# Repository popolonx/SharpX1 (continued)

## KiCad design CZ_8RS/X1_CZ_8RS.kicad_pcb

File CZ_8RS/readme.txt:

Kicad files (kicad version 5.1.5) for CZ-8RS RS-232 board.
Based on the http://www.x1center.org/resource/schematic/CZ8RS_Schematic.pdf
-at least one error corrected (IC6-pin4:  RESET -> IOEX )

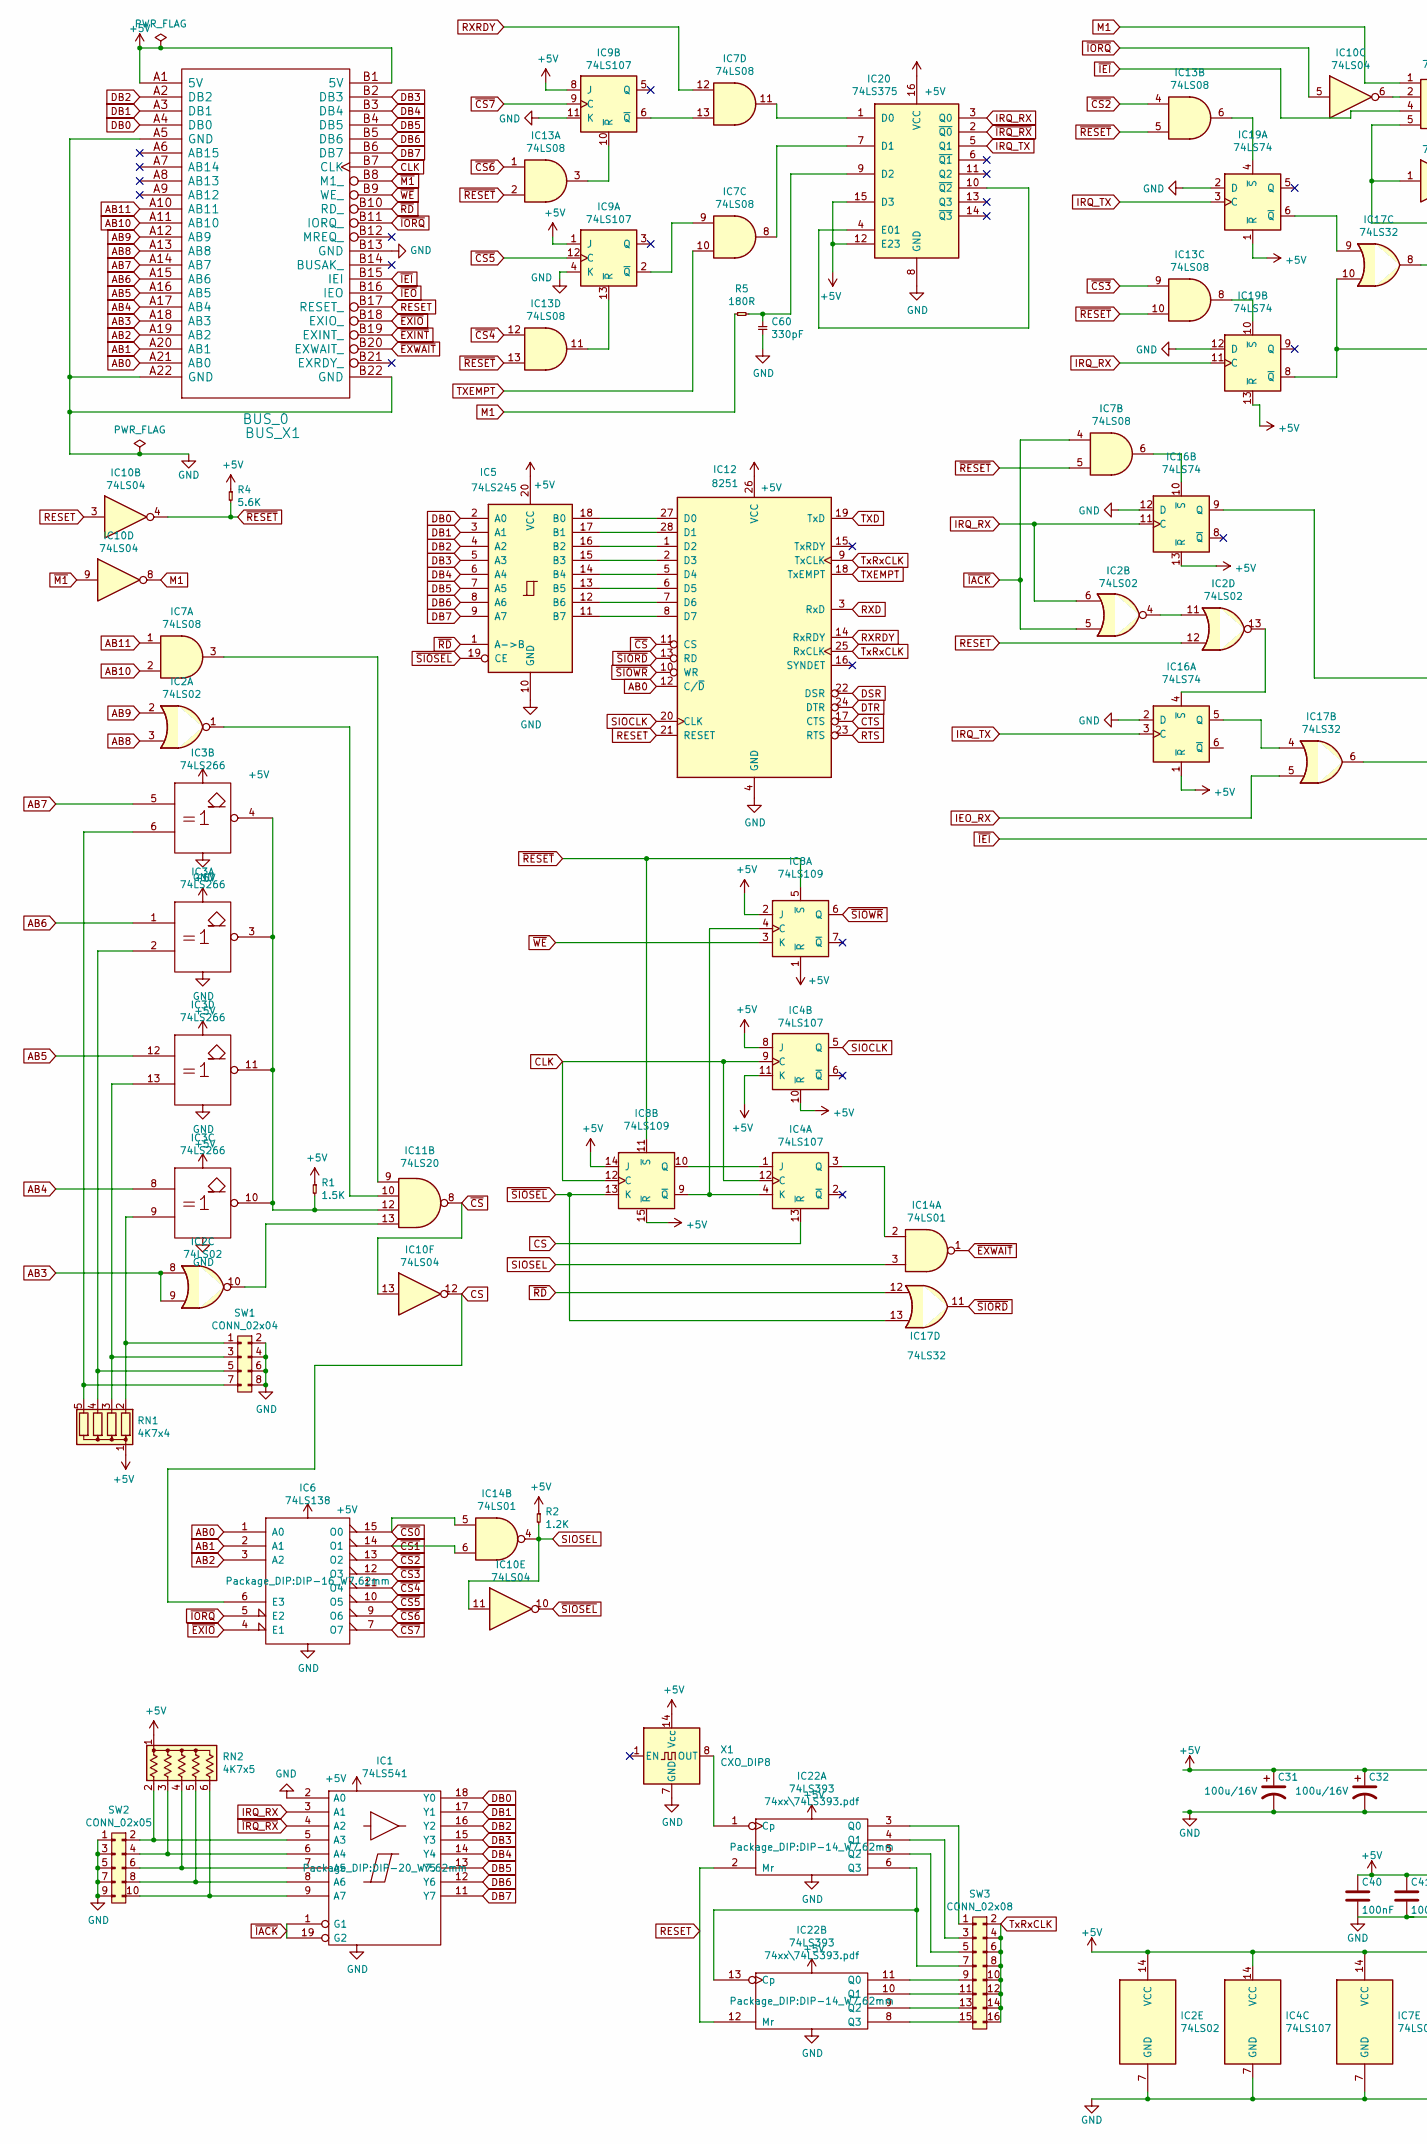
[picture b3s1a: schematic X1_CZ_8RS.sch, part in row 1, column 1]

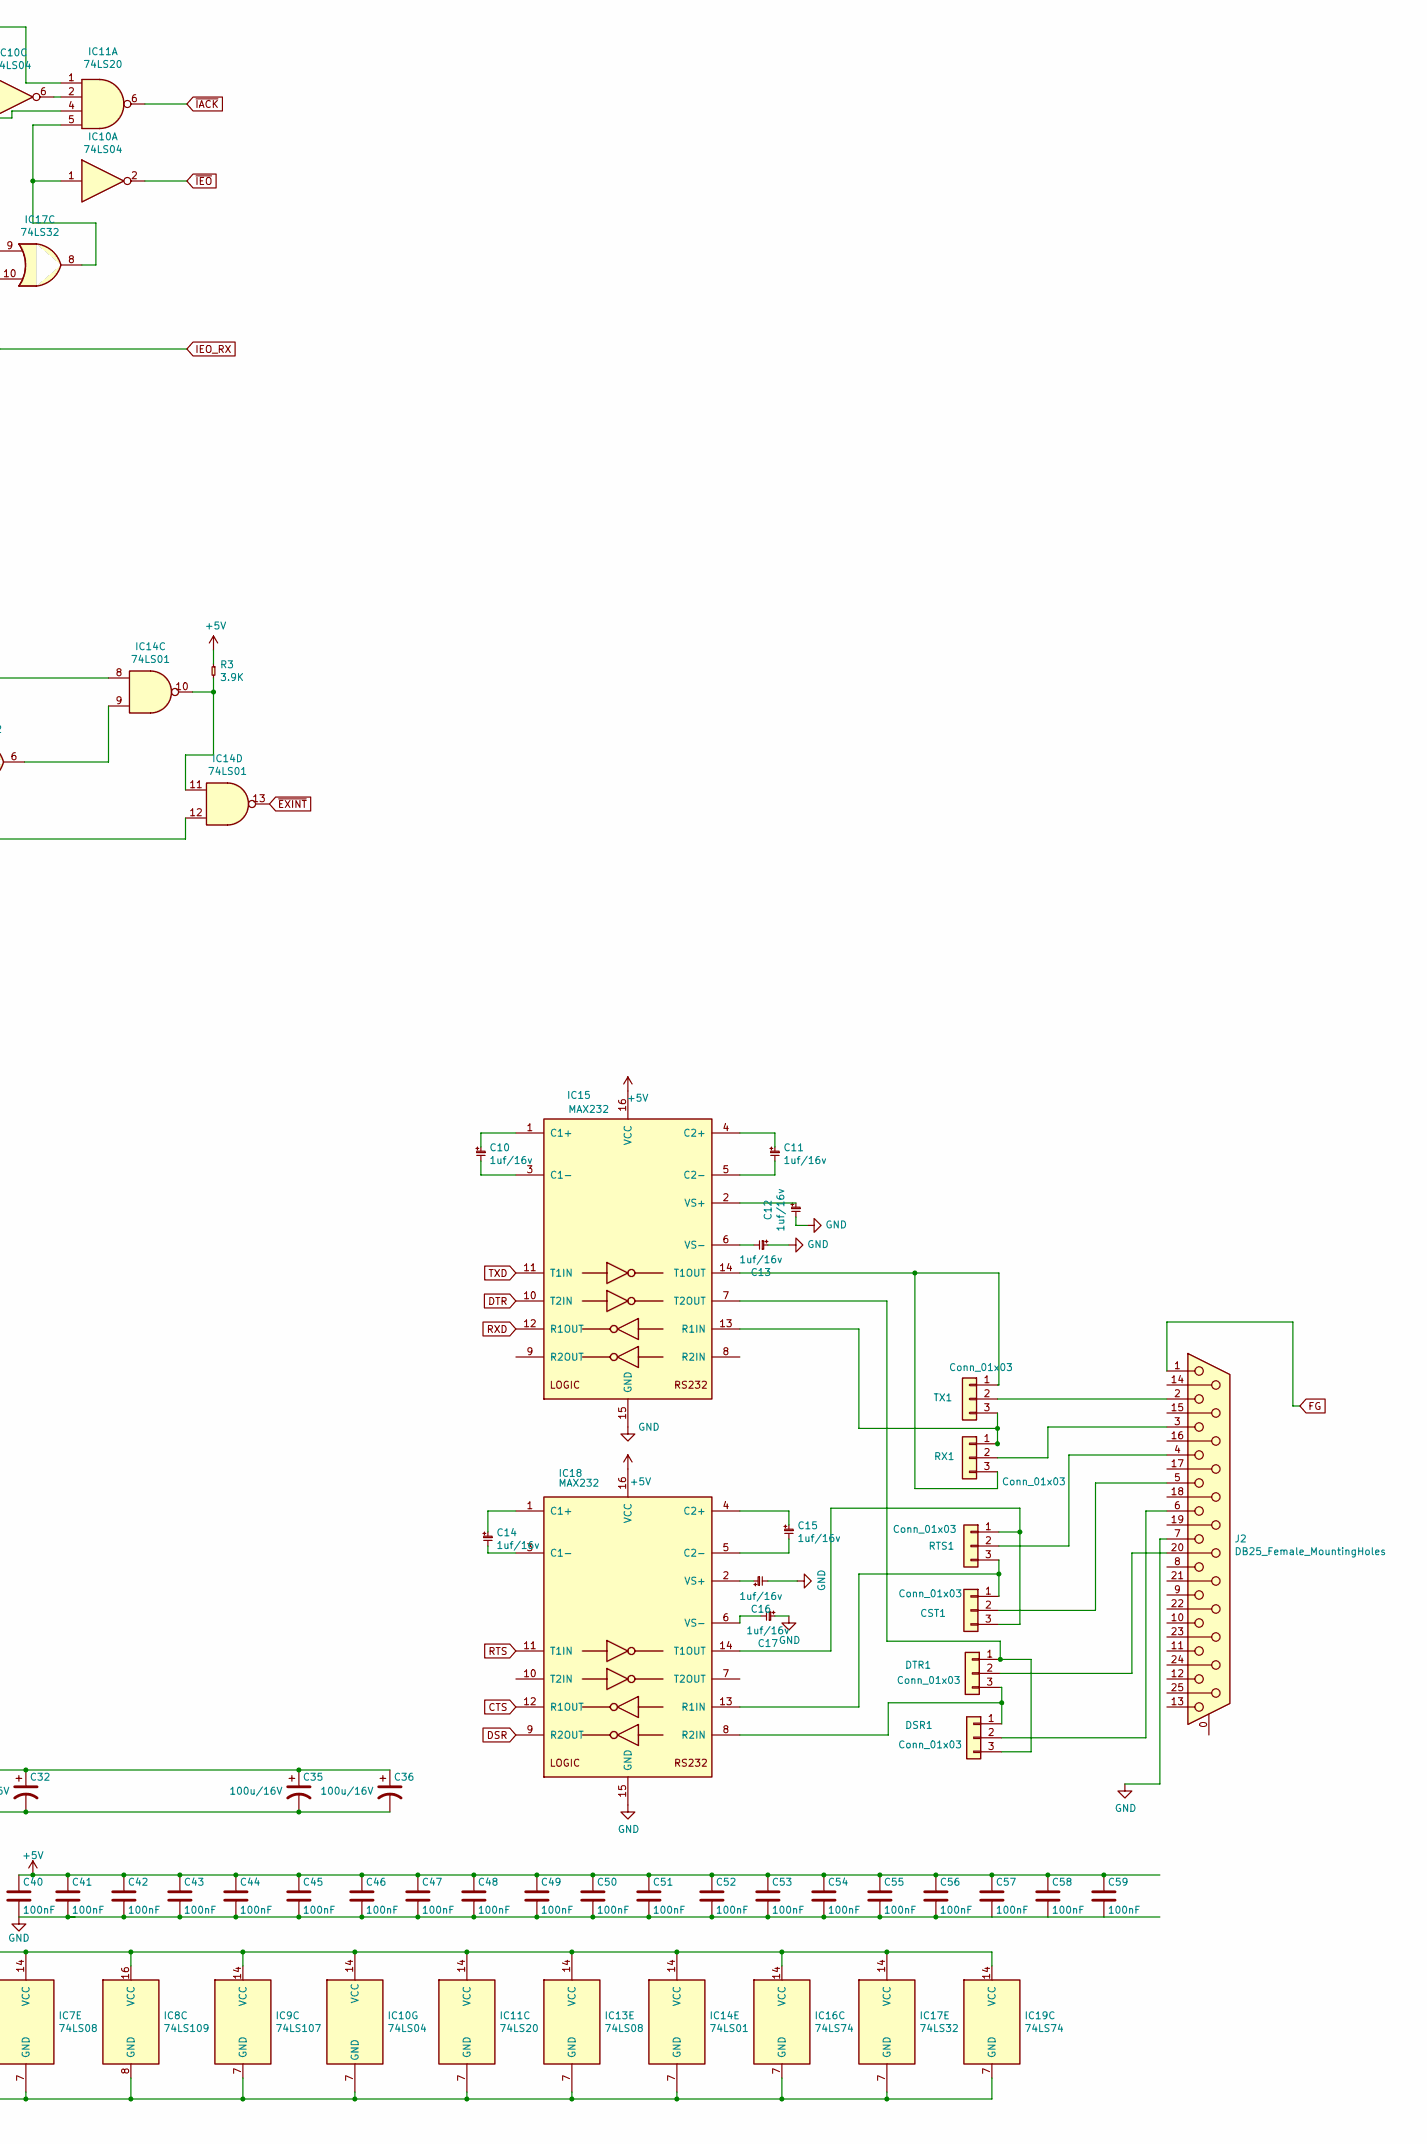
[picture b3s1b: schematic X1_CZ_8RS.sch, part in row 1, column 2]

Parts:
BUS_0: BUS_X1; X1_IO
C10, C11, C12, C13, C14, C15, C16, C17: 1uf/16v; CP_Radial_D8.0mm_P2.50mm
C31, C32, C35: 100u/16V; CP_Radial_D8.0mm_P5.00mm
C36: 100u/16V; CP_Radial_D7.5mm_P2.50mm
C40, C41, C42, C43, C44, C45, C46, C47, C48, C49, C50, C51, C52, C53, C54, C55, C56, C57, C58, C59: 100nF; C_Disc_D5.0mm_W2.5mm_P5.00mm
C60: 330pF; C_Disc_D5.0mm_W2.5mm_P5.00mm
CST1: Conn_01x03; PinHeader_1x03_P2.54mm_Vertical
DSR1: Conn_01x03; PinHeader_1x03_P2.54mm_Vertical
DTR1: Conn_01x03; PinHeader_1x03_P2.54mm_Vertical
IC1: 74LS541; DIP-20_W7.62mm
IC2: 74LS02; DIP-14_W7.62mm
IC3: 74LS266; DIP-14_W7.62mm
IC4, IC9: 74LS107; DIP-14_W7.62mm
IC5: 74LS245; DIP-20_W7.62mm
IC6: 74LS138; DIP-16_W7.62mm
IC7, IC13: 74LS08; DIP-14_W7.62mm
IC8: 74LS109; DIP-16_W7.62mm
IC10: 74LS04; DIP-14_W7.62mm
IC11: 74LS20; DIP-14_W7.62mm
IC12: 8251; DIP-28_W15.24mm
IC14: 74LS01; DIP-14_W7.62mm
IC15, IC18: MAX232; DIP-16_W7.62mm
IC16, IC19: 74LS74; DIP-14_W7.62mm
IC17: 74LS32; DIP-14_W7.62mm
IC20: 74LS375; DIP-16_W7.62mm
IC22: 74LS393; DIP-14_W7.62mm
J2: DB25_Female_MountingHoles; DSUB-25_Female_Horizontal_P2.77x2.84mm_EdgePinOffset4.94mm_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
R1: 1.5K; R_Axial_DIN0309_L9.0mm_D3.2mm_P12.70mm_Horizontal
R2: 1.2K; R_Axial_DIN0309_L9.0mm_D3.2mm_P12.70mm_Horizontal
R3: 3.9K; R_Axial_DIN0309_L9.0mm_D3.2mm_P12.70mm_Horizontal
R4: 5.6K; R_Axial_DIN0309_L9.0mm_D3.2mm_P12.70mm_Horizontal
R5: 180R; R_Axial_DIN0309_L9.0mm_D3.2mm_P12.70mm_Horizontal
RN1: 4K7x4; R_Array_SIP5
RN2: 4K7x5; R_Array_SIP6
RTS1: Conn_01x03; PinHeader_1x03_P2.54mm_Vertical
RX1: Conn_01x03; PinHeader_1x03_P2.54mm_Vertical
SW1: CONN_02x04; PinHeader_2x04_P2.54mm_Vertical
SW2: CONN_02x05; PinHeader_2x05_P2.54mm_Vertical
SW3: CONN_02x08; PinHeader_2x08_P2.54mm_Vertical
TX1: Conn_01x03; PinHeader_1x03_P2.54mm_Vertical
X1: CXO_DIP8; Oscillator_DIP-14

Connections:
+5V: BUS_0.A1 (5V), BUS_0.B1 (5V), C31.1, C32.1, C35.1, C36.1, C40.1, C41.1, C42.1, C43.1, C44.1, C45.1, C46.1, C47.1, C48.1, C49.1, C50.1, C51.1, C52.1, C53.1, C54.1, C55.1, C56.1, C57.1, C58.1, C59.1, IC1.20 (VCC), IC2.14 (VCC), IC3.14 (VCC), IC4.8 (J), IC4.10 (~R), IC4.11 (K), IC4.14 (VCC), IC5.20 (VCC), IC6.16 (VCC), IC7.14 (VCC), IC8.1 (~R), IC8.2 (J), IC8.14 (J), IC8.15 (~R), IC8.16 (VCC), IC9.1 (J), IC9.8 (J), IC9.14 (VCC), IC10.14 (VCC), IC11.14 (VCC), IC12.26 (VCC), IC13.14 (VCC), IC14.14 (VCC), IC15.16 (VCC), IC16.1 (~R), IC16.13 (~R), IC16.14 (VCC), IC17.14 (VCC), IC18.16 (VCC), IC19.1 (~R), IC19.13 (~R), IC19.14 (VCC), IC20.12 (E23), IC20.15 (D3), IC20.16 (VCC), IC22.14 (VCC), R1.1, R2.1, R3.1, R4.1, RN1.1 (common), RN2.1 (common), X1.14 (Vcc)
AB0: BUS_0.A21 (AB0), IC6.1 (A0), IC12.12 (C/~D)
AB1: BUS_0.A20 (AB1), IC6.2 (A1)
AB2: BUS_0.A19 (AB2), IC6.3 (A2)
AB3: BUS_0.A18 (AB3), IC2.8, IC2.9
AB4: BUS_0.A17 (AB4), IC3.8
AB5: BUS_0.A16 (AB5), IC3.12
AB6: BUS_0.A15 (AB6), IC3.1
AB7: BUS_0.A14 (AB7), IC3.5
AB8: BUS_0.A13 (AB8), IC2.3
AB9: BUS_0.A12 (AB9), IC2.2
AB10: BUS_0.A11 (AB10), IC7.2
AB11: BUS_0.A10 (AB11), IC7.1
CLK: BUS_0.B7 (CLK), IC4.9 (C), IC4.12 (C), IC8.12 (C)
CS: IC4.13 (~R), IC6.6 (E3), IC10.12
CTS: IC12.17 (CTS), IC18.12 (R1OUT)
DB0: BUS_0.A4 (DB0), IC1.18 (Y0), IC5.2 (A0)
DB1: BUS_0.A3 (DB1), IC1.17 (Y1), IC5.3 (A1)
DB2: BUS_0.A2 (DB2), IC1.16 (Y2), IC5.4 (A2)
DB3: BUS_0.B2 (DB3), IC1.15 (Y3), IC5.5 (A3)
DB4: BUS_0.B3 (DB4), IC1.14 (Y4), IC5.6 (A4)
DB5: BUS_0.B4 (DB5), IC1.13 (Y5), IC5.7 (A5)
DB6: BUS_0.B5 (DB6), IC1.12 (Y6), IC5.8 (A6)
DB7: BUS_0.B6 (DB7), IC1.11 (Y7), IC5.9 (A7)
DSR: IC12.22 (DSR), IC18.9 (R2OUT)
DTR: IC12.24 (DTR), IC15.10 (T2IN)
GND: BUS_0.A5 (GND), BUS_0.A22 (GND), BUS_0.B13 (GND), BUS_0.B22 (GND), C12.1, C13.2, C16.1, C17.2, C31.2, C32.2, C35.2, C36.2, C40.2, C41.2, C42.2, C43.2, C44.2, C45.2, C46.2, C47.2, C48.2, C49.2, C50.2, C51.2, C52.2, C53.2, C54.2, C55.2, C56.2, C57.2, C58.2, C59.2, C60.2, IC1.2 (A0), IC1.10 (GND), IC2.7 (GND), IC3.7 (GND), IC4.7 (GND), IC5.10 (GND), IC6.8 (GND), IC7.7 (GND), IC8.8 (GND), IC9.4 (K), IC9.7 (GND), IC9.11 (K), IC10.7 (GND), IC11.7 (GND), IC12.4 (GND), IC13.7 (GND), IC14.7 (GND), IC15.15 (GND), IC16.2 (D), IC16.7 (GND), IC16.12 (D), IC17.7 (GND), IC18.15 (GND), IC19.2 (D), IC19.7 (GND), IC19.12 (D), IC20.8 (GND), IC22.7 (GND), J2.7, SW1.2, SW1.4, SW1.6, SW1.8, SW2.1, SW2.3, SW2.5, SW2.7, SW2.9, X1.7 (GND)
IEO_RX: IC17.5, IC17.10, IC19.8 (~Q)
IRQ_RX: IC1.3 (A1), IC2.6, IC16.11 (C), IC19.11 (C), IC20.3 (Q0)
IRQ_TX: IC16.3 (C), IC19.3 (C), IC20.5 (Q1)
M1: IC10.8, IC11.1, R5.1
unnamed: C10.1, IC15.3 (C1-)
unnamed: C10.2, IC15.1 (C1+)
unnamed: C11.1, IC15.5 (C2-)
unnamed: C11.2, IC15.4 (C2+)
unnamed: C12.2, IC15.2 (VS+)
unnamed: C13.1, IC15.6 (VS-)
unnamed: C14.1, IC18.3 (C1-)
unnamed: C14.2, IC18.1 (C1+)
unnamed: C15.1, IC18.5 (C2-)
unnamed: C15.2, IC18.4 (C2+)
unnamed: C16.2, IC18.2 (VS+)
unnamed: C17.1, IC18.6 (VS-)
unnamed: C60.1, IC20.9 (D2), R5.2
unnamed: CST1.1, IC18.13 (R1IN), RTS1.3
unnamed: CST1.2, J2.5
unnamed: CST1.3, IC18.14 (T1OUT), RTS1.1
unnamed: DSR1.1, DTR1.3, IC18.8 (R2IN)
unnamed: DSR1.2, J2.6
unnamed: DSR1.3, DTR1.1, IC15.7 (T2OUT)
unnamed: DTR1.2, J2.20
unnamed: IC1.5 (A3), RN2.2 (R1), SW2.2
unnamed: IC1.6 (A4), RN2.3 (R2), SW2.4
unnamed: IC1.7 (A5), RN2.4 (R3), SW2.6
unnamed: IC1.8 (A6), RN2.5 (R4), SW2.8
unnamed: IC1.9 (A7), RN2.6 (R5), SW2.10
unnamed: IC2.4, IC2.11
unnamed: IC3.2, RN1.4 (R3), SW1.5
unnamed: IC3.6, RN1.5 (R4), SW1.7
unnamed: IC3.9, RN1.2 (R1), SW1.1
unnamed: IC3.13, RN1.3 (R2), SW1.3
unnamed: IC4.1 (J), IC8.10 (Q)
unnamed: IC4.4 (K), IC8.4 (C), IC8.9 (~Q)
unnamed: IC7.9, IC9.2 (~Q)
unnamed: IC7.13, IC9.6 (~Q)
unnamed: IC10.1, IC11.5, IC17.8
unnamed: IC10.6, IC11.2
unnamed: IC7.3, IC11.9
unnamed: IC2.1, IC11.10
unnamed: IC3.3, IC3.4, IC3.10, IC3.11, IC11.12, R1.2
unnamed: IC2.10, IC11.13
unnamed: IC5.16 (B2), IC12.1 (D2)
unnamed: IC5.15 (B3), IC12.2 (D3)
unnamed: IC5.14 (B4), IC12.5 (D4)
unnamed: IC5.13 (B5), IC12.6 (D5)
unnamed: IC5.12 (B6), IC12.7 (D6)
unnamed: IC5.11 (B7), IC12.8 (D7)
unnamed: IC5.18 (B0), IC12.27 (D0)
unnamed: IC5.17 (B1), IC12.28 (D1)
unnamed: IC9.10 (~R), IC13.3
unnamed: IC13.6, IC19.4 (~S)
unnamed: IC13.8, IC19.10 (~S)
unnamed: IC9.13 (~R), IC13.11
unnamed: IC4.3 (Q), IC14.2
unnamed: IC14.8, IC16.9 (Q)
unnamed: IC14.9, IC17.6
unnamed: IC14.10, IC14.11, R3.2
unnamed: IC15.13 (R1IN), RX1.1, TX1.3
unnamed: IC15.14 (T1OUT), RX1.3, TX1.1
unnamed: IC2.13, IC16.4 (~S)
unnamed: IC16.5 (Q), IC17.4
unnamed: IC7.6, IC16.10 (~S)
unnamed: IC17.9, IC19.6 (~Q)
unnamed: IC7.11, IC20.1 (D0)
unnamed: IC7.8, IC20.7 (D1)
unnamed: IC20.4 (E01), IC20.10 (~Q2)
unnamed: IC22.1 (Cp), X1.8 (OUT)
unnamed: IC22.3 (Q0), SW3.1
unnamed: IC22.4 (Q1), SW3.3
unnamed: IC22.5 (Q2), SW3.5
unnamed: IC22.8 (Q3), SW3.15
unnamed: IC22.9 (Q2), SW3.13
unnamed: IC22.10 (Q1), SW3.11
unnamed: IC22.11 (Q0), SW3.9
unnamed: IC22.6 (Q3), IC22.13 (Cp), SW3.7
unnamed: J2.2, TX1.2
unnamed: J2.3, RX1.2
unnamed: J2.4, RTS1.2
RESET: BUS_0.B17 (RESET_), IC2.12, IC10.3, IC12.21 (RESET), IC22.2 (Mr), IC22.12 (Mr)
RTS: IC12.23 (RTS), IC18.11 (T1IN)
RXD: IC12.3 (RxD), IC15.12 (R1OUT)
RXRDY: IC7.12, IC12.14 (RxRDY)
SIOCLK: IC4.5 (Q), IC12.20 (CLK)
SIOSEL: IC10.11, IC14.3, IC14.4, R2.2
TXD: IC12.19 (TxD), IC15.11 (T1IN)
TXEMPT: IC7.10, IC12.18 (TxEMPT)
TxRxCLK: IC12.9 (TxCLK), IC12.25 (RxCLK), SW3.2, SW3.4, SW3.6, SW3.8, SW3.10, SW3.12, SW3.14, SW3.16
~CS: IC10.13, IC11.8, IC12.11 (CS)
~CS0: IC6.15 (O0), IC14.5
~CS1: IC6.14 (O1), IC14.6
~CS2: IC6.13 (O2), IC13.4
~CS3: IC6.12 (O3), IC13.9
~CS4: IC6.11 (O4), IC13.12
~CS5: IC6.10 (O5), IC9.12 (C)
~CS6: IC6.9 (O6), IC13.1
~CS7: IC6.7 (O7), IC9.9 (C)
~EXINT: BUS_0.B19 (EXINT_), IC14.13
~EXIO: BUS_0.B18 (EXIO_), IC6.4 (E1)
~EXWAIT: BUS_0.B20 (EXWAIT_), IC14.1
~IACK: IC1.1 (G1), IC1.19 (G2), IC2.5, IC7.4, IC11.6
~IEI: BUS_0.B15 (IEI), IC11.4, IC14.12
~IEO: BUS_0.B16 (IEO), IC10.2
~IORQ: BUS_0.B11 (IORQ_), IC6.5 (E2), IC10.5
~IRQ_RX: IC1.4 (A2), IC20.2 (~Q0)
~M1: BUS_0.B8 (M1_), IC10.9
~RD: BUS_0.B10 (RD_), IC5.1 (A->B), IC17.12
~RESET: IC7.5, IC8.5 (~S), IC8.11 (~S), IC10.4, IC13.2, IC13.5, IC13.10, IC13.13, R4.2
~SIORD: IC12.13 (RD), IC17.11
~SIOSEL: IC5.19 (CE), IC8.13 (K), IC10.10, IC17.13
~SIOWR: IC8.6 (Q), IC12.10 (WR)
~WE: BUS_0.B9 (WE_), IC8.3 (K)

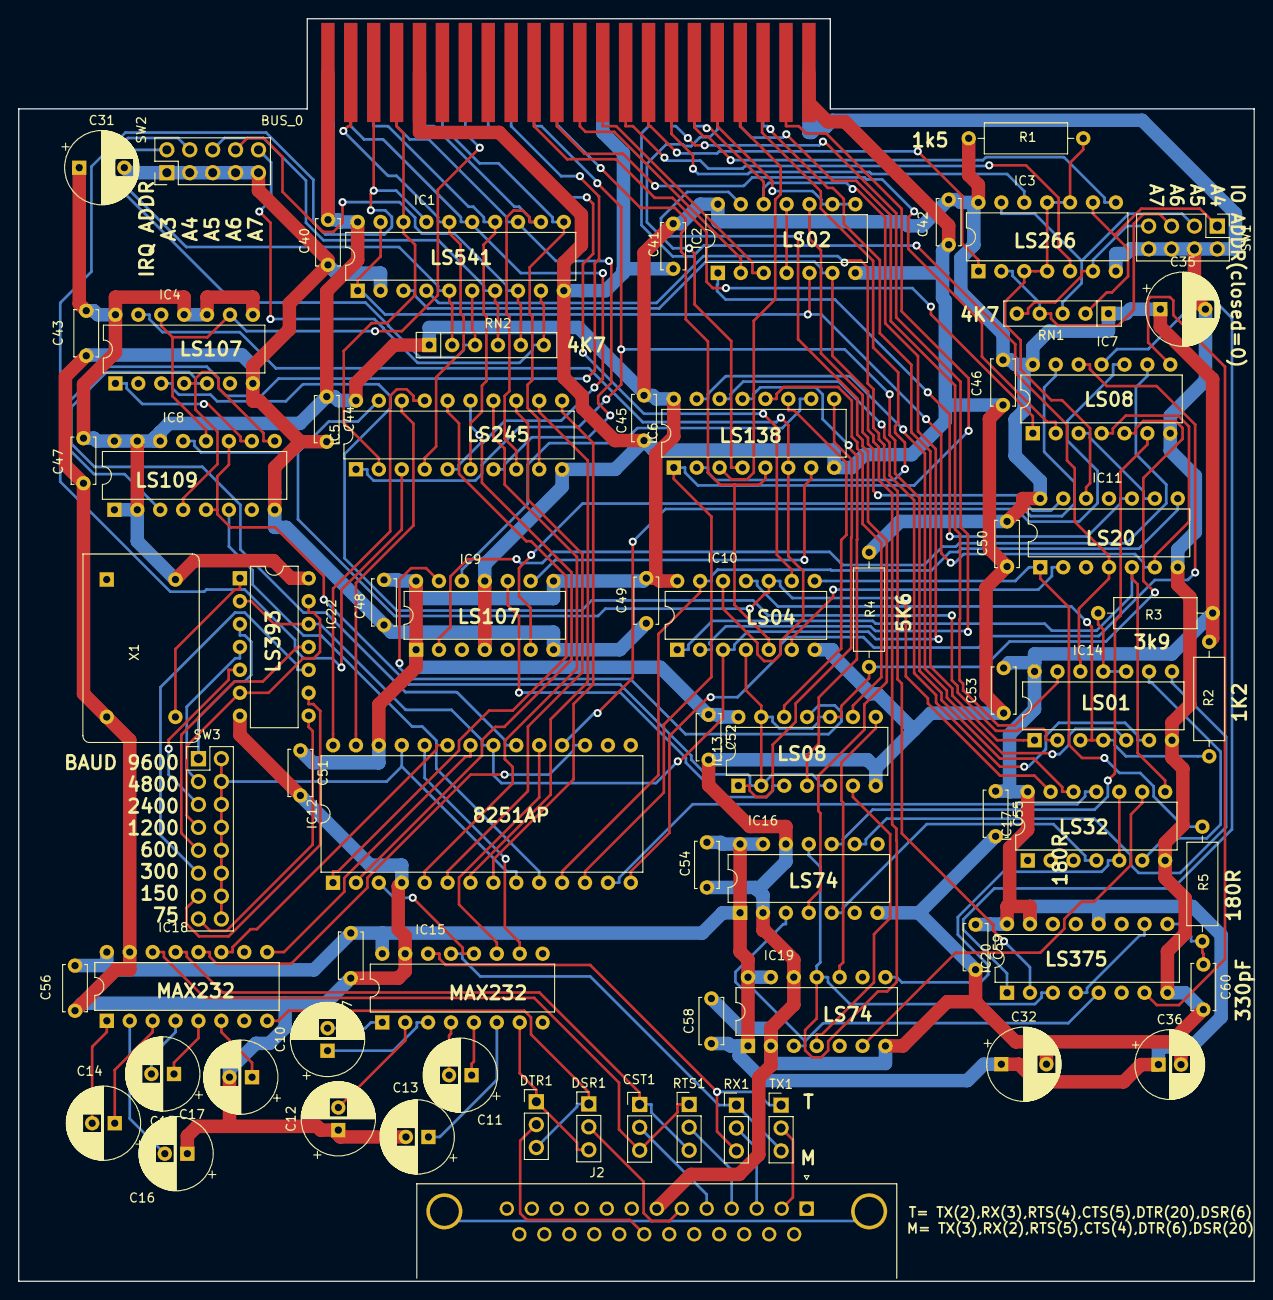
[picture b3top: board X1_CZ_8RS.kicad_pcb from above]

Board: 2 copper layers, 137.0 x 140.0 mm, 73 parts (0 on the bottom side), 141 nets.

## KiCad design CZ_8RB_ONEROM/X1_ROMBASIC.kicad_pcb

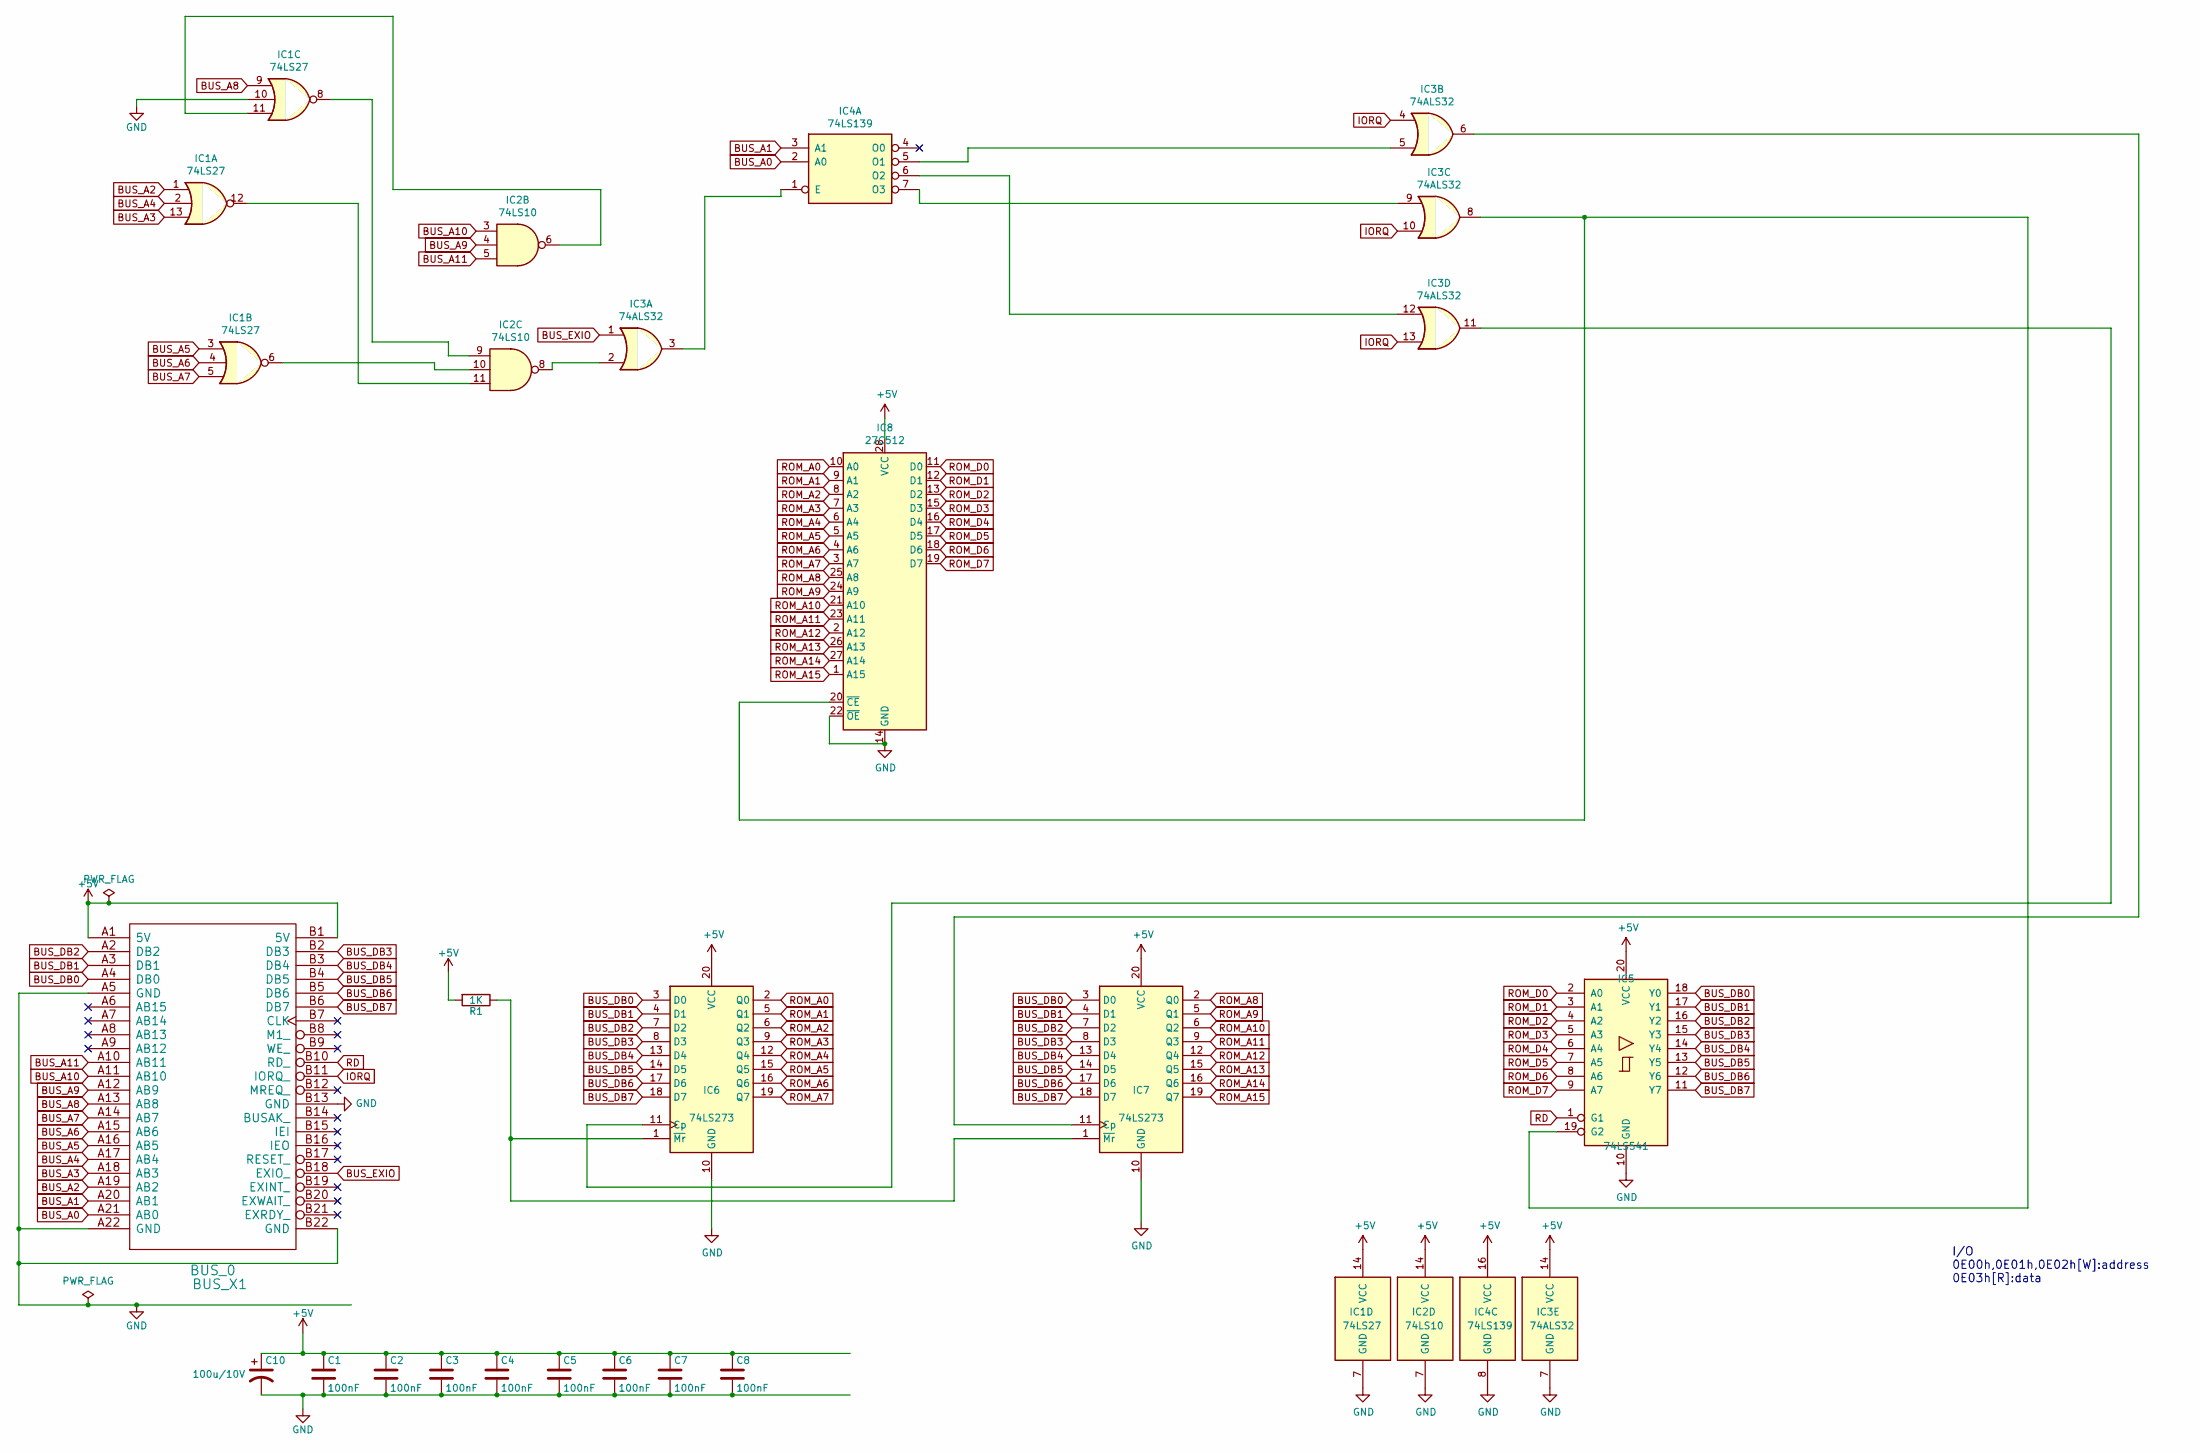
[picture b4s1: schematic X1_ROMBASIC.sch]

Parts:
BUS_0: BUS_X1; X1_IO
C1, C2, C3, C4, C5, C6, C7, C8: 100nF; C_Disc_D5.0mm_W2.5mm_P5.00mm
C10: 100u/10V; CP_Radial_D8.0mm_P5.00mm
IC1: 74LS27; DIP-14_W7.62mm
IC2: 74LS10; DIP-14_W7.62mm
IC3: 74ALS32; DIP-14_W7.62mm
IC4: 74LS139; DIP-16_W7.62mm
IC5: 74LS541; DIP-20_W7.62mm
IC6, IC7: 74LS273; DIP-20_W7.62mm
IC8: 27C512; DIP-28_W15.24mm
R1: 1K; R_Axial_DIN0207_L6.3mm_D2.5mm_P10.16mm_Horizontal

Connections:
+5V: BUS_0.A1 (5V), BUS_0.B1 (5V), C1.1, C2.1, C3.1, C4.1, C5.1, C6.1, C7.1, C8.1, C10.1, IC1.14 (VCC), IC2.14 (VCC), IC3.14 (VCC), IC4.16 (VCC), IC5.20 (VCC), IC6.20 (VCC), IC7.20 (VCC), IC8.28 (VCC), R1.2
BUS_A0: BUS_0.A21 (AB0), IC4.2 (A0)
BUS_A1: BUS_0.A20 (AB1), IC4.3 (A1)
BUS_A2: BUS_0.A19 (AB2), IC1.1
BUS_A3: BUS_0.A18 (AB3), IC1.13
BUS_A4: BUS_0.A17 (AB4), IC1.2
BUS_A5: BUS_0.A16 (AB5), IC1.3
BUS_A6: BUS_0.A15 (AB6), IC1.4
BUS_A7: BUS_0.A14 (AB7), IC1.5
BUS_A8: BUS_0.A13 (AB8), IC1.9
BUS_A9: BUS_0.A12 (AB9), IC2.4
BUS_A10: BUS_0.A11 (AB10), IC2.3
BUS_A11: BUS_0.A10 (AB11), IC2.5
BUS_DB0: BUS_0.A4 (DB0), IC5.18 (Y0), IC6.3 (D0), IC7.3 (D0)
BUS_DB1: BUS_0.A3 (DB1), IC5.17 (Y1), IC6.4 (D1), IC7.4 (D1)
BUS_DB2: BUS_0.A2 (DB2), IC5.16 (Y2), IC6.7 (D2), IC7.7 (D2)
BUS_DB3: BUS_0.B2 (DB3), IC5.15 (Y3), IC6.8 (D3), IC7.8 (D3)
BUS_DB4: BUS_0.B3 (DB4), IC5.14 (Y4), IC6.13 (D4), IC7.13 (D4)
BUS_DB5: BUS_0.B4 (DB5), IC5.13 (Y5), IC6.14 (D5), IC7.14 (D5)
BUS_DB6: BUS_0.B5 (DB6), IC5.12 (Y6), IC6.17 (D6), IC7.17 (D6)
BUS_DB7: BUS_0.B6 (DB7), IC5.11 (Y7), IC6.18 (D7), IC7.18 (D7)
BUS_EXIO: BUS_0.B18 (EXIO_), IC3.1
GND: BUS_0.A5 (GND), BUS_0.A22 (GND), BUS_0.B13 (GND), BUS_0.B22 (GND), C1.2, C2.2, C3.2, C4.2, C5.2, C6.2, C7.2, C8.2, C10.2, IC1.7 (GND), IC1.10, IC2.7 (GND), IC3.7 (GND), IC4.8 (GND), IC5.10 (GND), IC6.10 (GND), IC7.10 (GND), IC8.14 (GND), IC8.22 (~OE)
IORQ: BUS_0.B11 (IORQ_), IC3.4, IC3.10, IC3.13
unnamed: IC1.6, IC2.10
unnamed: IC1.8, IC2.9
unnamed: IC1.11, IC2.6
unnamed: IC1.12, IC2.11
unnamed: IC2.8, IC3.2
unnamed: IC3.3, IC4.1 (E)
unnamed: IC3.5, IC4.5 (O1)
unnamed: IC3.6, IC7.11 (Cp)
unnamed: IC3.8, IC5.19 (G2), IC8.20 (~CE)
unnamed: IC3.9, IC4.7 (O3)
unnamed: IC3.11, IC6.11 (Cp)
unnamed: IC3.12, IC4.6 (O2)
unnamed: IC6.1 (~Mr), IC7.1 (~Mr), R1.1
RD: BUS_0.B10 (RD_), IC5.1 (G1)
ROM_A0: IC6.2 (Q0), IC8.10 (A0)
ROM_A1: IC6.5 (Q1), IC8.9 (A1)
ROM_A2: IC6.6 (Q2), IC8.8 (A2)
ROM_A3: IC6.9 (Q3), IC8.7 (A3)
ROM_A4: IC6.12 (Q4), IC8.6 (A4)
ROM_A5: IC6.15 (Q5), IC8.5 (A5)
ROM_A6: IC6.16 (Q6), IC8.4 (A6)
ROM_A7: IC6.19 (Q7), IC8.3 (A7)
ROM_A8: IC7.2 (Q0), IC8.25 (A8)
ROM_A9: IC7.5 (Q1), IC8.24 (A9)
ROM_A10: IC7.6 (Q2), IC8.21 (A10)
ROM_A11: IC7.9 (Q3), IC8.23 (A11)
ROM_A12: IC7.12 (Q4), IC8.2 (A12)
ROM_A13: IC7.15 (Q5), IC8.26 (A13)
ROM_A14: IC7.16 (Q6), IC8.27 (A14)
ROM_A15: IC7.19 (Q7), IC8.1 (A15)
ROM_D0: IC5.2 (A0), IC8.11 (D0)
ROM_D1: IC5.3 (A1), IC8.12 (D1)
ROM_D2: IC5.4 (A2), IC8.13 (D2)
ROM_D3: IC5.5 (A3), IC8.15 (D3)
ROM_D4: IC5.6 (A4), IC8.16 (D4)
ROM_D5: IC5.7 (A5), IC8.17 (D5)
ROM_D6: IC5.8 (A6), IC8.18 (D6)
ROM_D7: IC5.9 (A7), IC8.19 (D7)

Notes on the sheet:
I/O 0E00h,0E01h,0E02h[W]:address 0E03h[R]:data

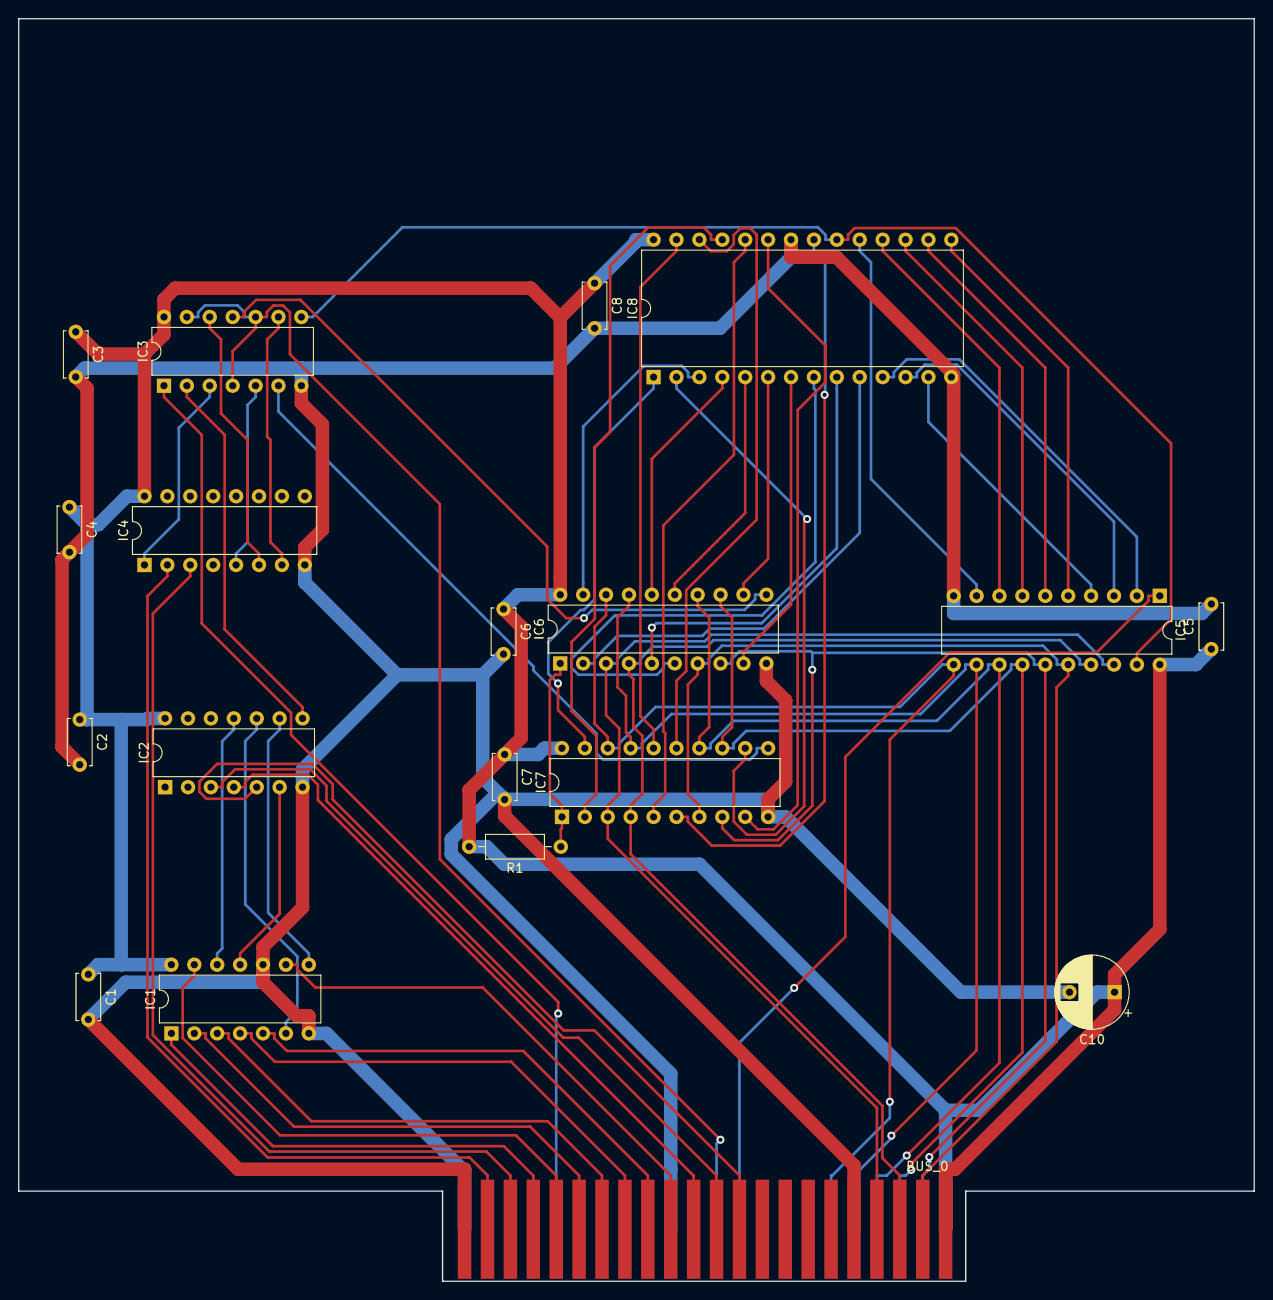
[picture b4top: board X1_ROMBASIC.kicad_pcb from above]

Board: 2 copper layers, 137.0 x 140.0 mm, 19 parts (0 on the bottom side), 62 nets.

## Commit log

2024-04-13 corrected siosel, siord, and siowr line tag names
2024-04-14 corrected rx/tx mapping
    corrected rx/tx mapping betwene atmega328p and 8251
2024-04-14 added component names and jumper values
2024-05-28 some small addition
2024-06-03 small update to schematics
2024-06-04 added more schematics
2024-06-04 added some more schematics
2024-06-08 more schematics drawn
2024-06-09 more schematics added
2024-06-10 added more schematics
    almoust done with the main board schematics.
2024-06-13 adding transistor and capacitor lists as txt files
2024-06-13 added c811 capacitor to the list
2024-06-14 added more schematics
    now all ICs from mainboard shuold be in the schematics, but some connections are missing. Also resistor values are missing
2024-06-14 some missing connection added
2024-06-14 transistor types added and corrections...
2024-06-14 changed Q102 to D102 (1SV55 type)
2024-06-15 added resistor list
2024-06-15 updated capa/resistor lists. Added J1/J2/K1/K2
2024-06-16 added power supply schematics
2024-06-16 updated resistor list
2024-06-16 add one backpanel pcb
    added backpanel pcb that has adjustable resistors, L1-3 and I1-5 are coming here
2024-06-16 added N-connector RGB21 target pins
2024-06-16 added H-connector pins
    added H-connector pins and external DSUB joystick port pinout command mapping
2024-06-16 added front panel stuff
    added front panel slider and led stuff
2024-06-16 added resistors/capacitors over the ICs
    added resistors/capacitors that are over the ICs, so soldered to component side IC legs.
2024-06-16 added some missing stuff
2024-06-16 double Q107 changed to Q102
2024-06-16 rearranged into inside page. Added pdf version.
2024-06-21 some comment texts updated in schematics
2024-06-21 added missing capacitors and corrected some
